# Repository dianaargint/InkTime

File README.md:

# InkTime

InkTime este un smartwatch open-source cu consum redus, realizat in jurul microcontroller-ului **nRF52840**. Proiectul include un **display e-paper**, alimentare din **baterie Li-Po**, **incarcare prin USB-C**, **monitorizare baterie**, **IMU** si **feedback haptic**.

Scopul proiectului a fost realizarea unei placi compacte care sa poata fi integrata intr-o carcasa dedicata si sa poata functiona din baterie, cu un consum cat mai mic.

# Diagrama bloc

```text
+-------------+      +----------------+      +------------------+
| USB-C       |----->| ESD Protection |----->| BQ25180 Charger  |
+-------------+      +----------------+      +--------+---------+
                                                        |
                                                        v
                                                +---------------+
                                                | Li-Po Battery |
                                                +---+-------+---+
                                                    |       |
                                                    |       v
                                                    |   +-----------+
                                                    |   | MAX17048  |
                                                    |   | FuelGauge |
                                                    |   +-----------+
                                                    v
                                              +-------------+
                                              | RT6160 DC/DC|
                                              +------+------+ 
                                                     |
                                                     v
                                              +-------------+
                                              | nRF52840    |
                                              | BLE MCU     |
                                              +------+------+-------------------+
                                                     |      |         |         |
                                                     |      |         |         |
                                                     v      v         v         v
                                              +--------+ +------+ +-------+ +--------+
                                              | E-Paper| | IMU  | |Haptic | | Buttons|
                                              +--------+ +------+ +---+---+ +--------+
                                                                        |
                                                                        v
                                                                   +---------+
                                                                   | Shaker  |
                                                                   +---------+

```

## Bill of Materials (BOM)

| Component | Value / Part Number | Package | Qty | Description | Datasheet |
| --------- | ------------------- | ------- | --- | ----------- | --------- |
| MCU | NRF52840_QF | NORDIC_NRF_4_AQFN50P700X700X85_HS-74N | 1 | Main BLE microcontroller | [Datasheet](https://infocenter.nordicsemi.com/pdf/nRF52840_PS_v1.1.pdf) |
| PMIC charger | BQ25180YBGR | BQ25180YBGR_BGA8C40P2X4_100X155X50 | 1 | Li-Po charger | [Datasheet](https://www.ti.com/lit/ds/symlink/bq25180.pdf) |
| DC/DC | RT6160AWSC | RT6160AWSC_BGA15C40P3X5_140X230X60 | 1 | Buck-boost DC/DC converter | [Datasheet](https://www.richtek.com/assets/product_file/RT6160A/DS6160A-05.pdf) |
| Fuel gauge | MAX17048G+T10 | ESP32_C6_LIBRARY_SON50P200X200X80-9N | 1 | Battery fuel gauge | [Datasheet](https://www.analog.com/media/en/technical-documentation/data-sheets/max17048-max17049.pdf) |
| IMU | BMA421 | BMA423_BMA423 | 1 | Triaxial accelerometer | [Datasheet](https://www.bosch-sensortec.com/products/motion-sensors/accelerometers/bma421/) |
| Haptic driver | DRV2605YZFR | DRV2605YZFR_BGA9C50P3X3_144X144X62 | 1 | Haptic driver for vibration motor | [Datasheet](https://www.ti.com/lit/ds/symlink/drv2605.pdf) |
| USB ESD | USBLC6-2SC6Y | ESP32_C6_LIBRARY_3_SOT95P280X145-6N | 1 | USB ESD protection | [Datasheet](https://www.st.com/resource/en/datasheet/usblc6-2.pdf) |
| Antenna | 2450AT18B100E | 2450AT18B100E_ANTC3216X140N | 1 | 2.4 GHz chip antenna | [Datasheet](https://www.johansontechnology.com/datasheets/antennas/2450AT18B100.pdf) |
| Display connector | 503480-2400 | 503480-2400_5034802400 | 1 | FPC connector for e-paper display | [Datasheet](https://www.molex.com/en-us/products/part-detail/5034802400) |
| USB-C | KH-TYPE-C-16P | KH-TYPE-C-16P_KINGHELM_KH-TYPE-C-16P | 1 | USB-C connector | - |
| Debug connector | TC2030-IDC | TC2030-IDC_TC2030IDC | 1 | SWD programming / debug connector | [Datasheet](https://www.tag-connect.com/product/tc2030-idc) |
| EPD MOSFET | SI1308EDL-T1-GE3 | ESP32_C6_LIBRARY_6_SOT65P210X110-3N | 1 | MOSFET used in e-paper drive stage | [Datasheet](https://www.vishay.com/docs/68986/si1308edl.pdf) |
| EPD MOSFET | DMG2305UX-7 | ESP32_C6_LIBRARY_4_ESP32_WROVER_SPARKFUN-DISCRETESEMI_MOSFET | 1 | MOSFET used in e-paper drive stage | [Datasheet](https://www.diodes.com/assets/Datasheets/DMG2305UX.pdf) |
| Schottky diode | MBR0530 | ESP32_C6_LIBRARY_5_SOD3716X135N | 3 | Schottky diode used in EPD boost stage | [Datasheet](https://www.onsemi.com/pdf/datasheet/mbr0530t1-d.pdf) |
| Power inductor | FTC252012SR47MBCA | MLP2016SR47MT0S1_INDC2016X100N | 1 | Inductor for RT6160 converter | [JLC Part](https://jlcpcb.com/partdetail/6763488-FTC252012SR47MBCA/C5832368) |
| EPD inductor | 68uH | ESP32_C6_LIBRARY_2_IND_4828-WE-TPC_WRE | 1 | Inductor for e-paper boost stage | - |
| RF inductor | 3.9nH | NORDIC_NRF_2_RESC0402_L | 1 | RF matching network | - |
| RF inductor | 15nH | NORDIC_NRF_2_RESC0402_L | 1 | RF filter / matching | - |
| Power inductor | 10uH | NORDIC_NRF_2_RESC0402_L | 1 | Power stage passive | - |
| HF crystal | 32MHz | NORDIC_NRF_BT-XTAL_2016_N | 1 | Main MCU clock | - |
| LF crystal | 32.768kHz | NORDIC_NRF_1_XTAL_3215_N | 1 | RTC / low-power clock | - |
| Buttons | EVP-AKE31A | 2025-10-22_07-23-44_LIBRARY_SW_EVP-AKE31A_PAN | 3 | Tactile user buttons | - |
| Solder jumper | SJ | ESP32_C6_LIBRARY_7_JUMPER_SJ | 1 | Configuration jumper | - |
| Test pads | HECTOR_WATCH_1_TPTP20R | HECTOR_WATCH_1_TP20R | 14 | Test points for debug / power / signals | - |

BOM-ul complet generat automat se gaseste in folderul Manufacturing.

## Pinii folositi de nRF52840

| Pin nRF52840 | Semnal | Componenta / destinatie | Rol |
| ------------ | ------ | ----------------------- | --- |
| P0.00 / XL1 | XL1 | Cristal 32.768kHz | clock low-power / RTC |
| P0.01 / XL2 | XL2 | Cristal 32.768kHz | clock low-power / RTC |
| P0.02 | SCK | Display e-paper | SPI clock pentru display |
| P0.03 | MOSI | Display e-paper | SPI data pentru display |
| P0.05 | EPD_CS | Display e-paper | chip select pentru display |
| P0.06 | SDA | BMA421 / DRV2605 / MAX17048 / BQ25180 / RT6160 | magistrala I2C comuna |
| P0.07 | SCL | BMA421 / DRV2605 / MAX17048 / BQ25180 / RT6160 | magistrala I2C comuna |
| P0.08 | IMU_INT1 | BMA421 | interrupt de la IMU |
| P0.10 | ALERT | MAX17048 | alerta fuel gauge |
| P0.11 | PMIC_INT | BQ25180YBGR | interrupt de la charger |
| P0.12 | HAPTIC_EN | DRV2605YZFR | enable pentru driverul haptic |
| P0.13 | SW_UP | Buton UP | input utilizator |
| P0.14 | SW_ENT | Buton ENTER | input utilizator |
| P0.15 | EPD_DC | Display e-paper | selectare data / command |
| P0.16 | EPD_RST | Display e-paper | reset display |
| P0.17 | EPD_BUSY | Display e-paper | busy status de la display |
| P0.18 / RESET | RESET | Sistem | reset hardware |
| P1.00 | SWO | Debug | trace output |
| P1.02 | SW_DN | Buton DOWN | input utilizator |
| P1.08 | IMU_INT2 | BMA421 | al doilea interrupt de la IMU |
| SWDIO | SWDIO | TC2030-IDC | programare / debug |
| SWDCLK | SWDCLK | TC2030-IDC | programare / debug |
| ANT | RF | Antena 2.4 GHz | transmisie BLE |
| VBUS | VBUS | USB-C | alimentare 5V |

Am ales pinii in asa fel incat sa separ cat mai clar liniile de comunicatie de semnalele de control. Display-ul foloseste SPI pentru transferul de date, iar semnalele EPD_CS, EPD_DC, EPD_RST si EPD_BUSY sunt separate pentru controlul corect al panoului. IMU-ul, fuel gauge-ul, charger-ul, convertorul DC/DC si driverul haptic folosesc aceeasi magistrala I2C, ceea ce reduce numarul de pini ocupati. Butoanele sunt puse pe GPIO-uri dedicate, iar liniile SWDIO, SWDCLK si SWO sunt folosite pentru programare si debugging.

## Descriere hardware
1. Microcontroller

Microcontroller-ul principal al proiectului este nRF52840 (U1). Acesta este componenta centrala a sistemului si se ocupa de:

comunicatia BLE, controlul display-ului e-paper, comunicatia cu senzorii si circuitele de power prin I2C, citirea butoanelor, controlul driverului haptic, interfata de debug SWD

Pentru clock sunt folosite doua cristale:

X1 = 32MHz
X2 = 32.768kHz

Cristalul de 32MHz este folosit pentru functionarea principala a MCU-ului si pentru partea de radio, iar cristalul de 32.768kHz este folosit pentru RTC si modurile low-power.

2. Alimentare si management energetic

Partea de alimentare am impartit-o in trei blocuri principale:

BQ25180YBGR

IC1 = BQ25180YBGR se ocupa de incarcarea bateriei Li-Po din USB-C. Intrarea de 5V vine din VBUS, iar iesirea merge spre baterie. Circuitul are si semnal de interrupt catre MCU pentru monitorizarea starii de incarcare.

MAX17048

U3 = MAX17048G+T10 monitorizeaza tensiunea bateriei si comunica prin I2C cu nRF52840. Are si semnal de alerta catre MCU pentru praguri critice sau schimbari de stare.

RT6160AWSC

IC9 = RT6160AWSC este convertorul buck-boost care genereaza alimentarea stabila 3V3 / VREG pentru sistem. Acesta este necesar deoarece tensiunea bateriei variaza in functie de starea de incarcare, iar sistemul are nevoie de o alimentare stabila.

3. Bateria

Am folosit o baterie de tip LP502030, 3.7V, aproximativ 250mAh. In proiect, bateria nu este conectata prin conector JST, ci direct la doua test pad-uri:

TP_VBAT, TP_BAT_GND

Am ales varianta asta ca sa economisesc spatiu si pentru ca asta era si cerinta proiectului.

4. Display e-paper

Display-ul este conectat prin conectorul 503480-2400 si este controlat prin:

SCK, MOSI, EPD_CS,EPD_DC, EPD_RST, EPD_BUSY

5. IMU

IMU-ul folosit este BMA421 (IC3) si comunica prin I2C. Are doua semnale de interrupt:

IMU_INT1
,IMU_INT2

Aceste semnale sunt conectate la MCU pentru detectarea rapida a evenimentelor de miscare si pentru trezirea sistemului din moduri low-power.

6. Haptic

Pentru feedback haptic este folosit DRV2605YZFR (IC2), care comanda motorul de vibratie. Comunicarea este facuta pe I2C, iar activarea poate fi controlata si printr-un semnal GPIO dedicat.

7. USB-C si protectie ESD

Conectorul J4 = KH-TYPE-C-16P este folosit pentru alimentare si optional pentru interfata USB. Protectia ESD este facuta cu USBLC6-2SC6Y, pentru a proteja liniile sensibile la descarcari electrostatice.

8. RF si antena

Antena este ANT1 = 2450AT18B100E si este conectata la pinul RF al nRF52840 printr-o retea de matching. Antena este pusa la marginea placii, iar sub ea am lasat zona fara plan de masa si fara trasee, conform regulilor de proiectare RF.

## PCB si layout
Board specifications
- dimensiunea placii: 46 mm x 35 mm
- grosimea PCB-ului: 1 mm
- componentele sunt plasate pe TOP
- rutarea este facuta pe Top si Bottom
- exista poligoane de GND pe Top si Bottom
  
Routing rules

- traseele de semnal au fost rutate cu minimum 0.15 mm
- traseele de putere au fost rutate cu 0.3 mm acolo unde spatiul a permis
- in zonele foarte dense, unele segmente scurte au trebuit ingustate local
  
Ground planes

Am folosit planuri de masa pe placa, iar in zonele importante am pus si via stitching, mai ales in jurul zonei RF si al microcontroller-ului.

Antena si keepout

Antena este pusa la marginea PCB-ului, iar sub ea:

- nu exista plan de masa
- nu exista trasee
- nu exista turnare de cupru

Acest lucru a fost facut pentru a nu afecta performanta RF.
Pe parcursul proiectarii au aparut mai multe probleme, mai ales in zonele cu densitate mare de componente:

- zona din jurul nRF52840 a fost dificil de rutat
- integrarea bateriei, display-ului si shaker-ului in acelasi volum a fost dificila

## Integrare mecanica si 3D

In modelul 3D au fost incluse:
- PCB-ul
- carcasa
- bateria
- display-ul
- shaker-ul

Au fost verificate:
- alinierea USB-C
- alinierea butoanelor
- pozitia display-ului fata de carcasa
- spatiul pentru baterie si shaker

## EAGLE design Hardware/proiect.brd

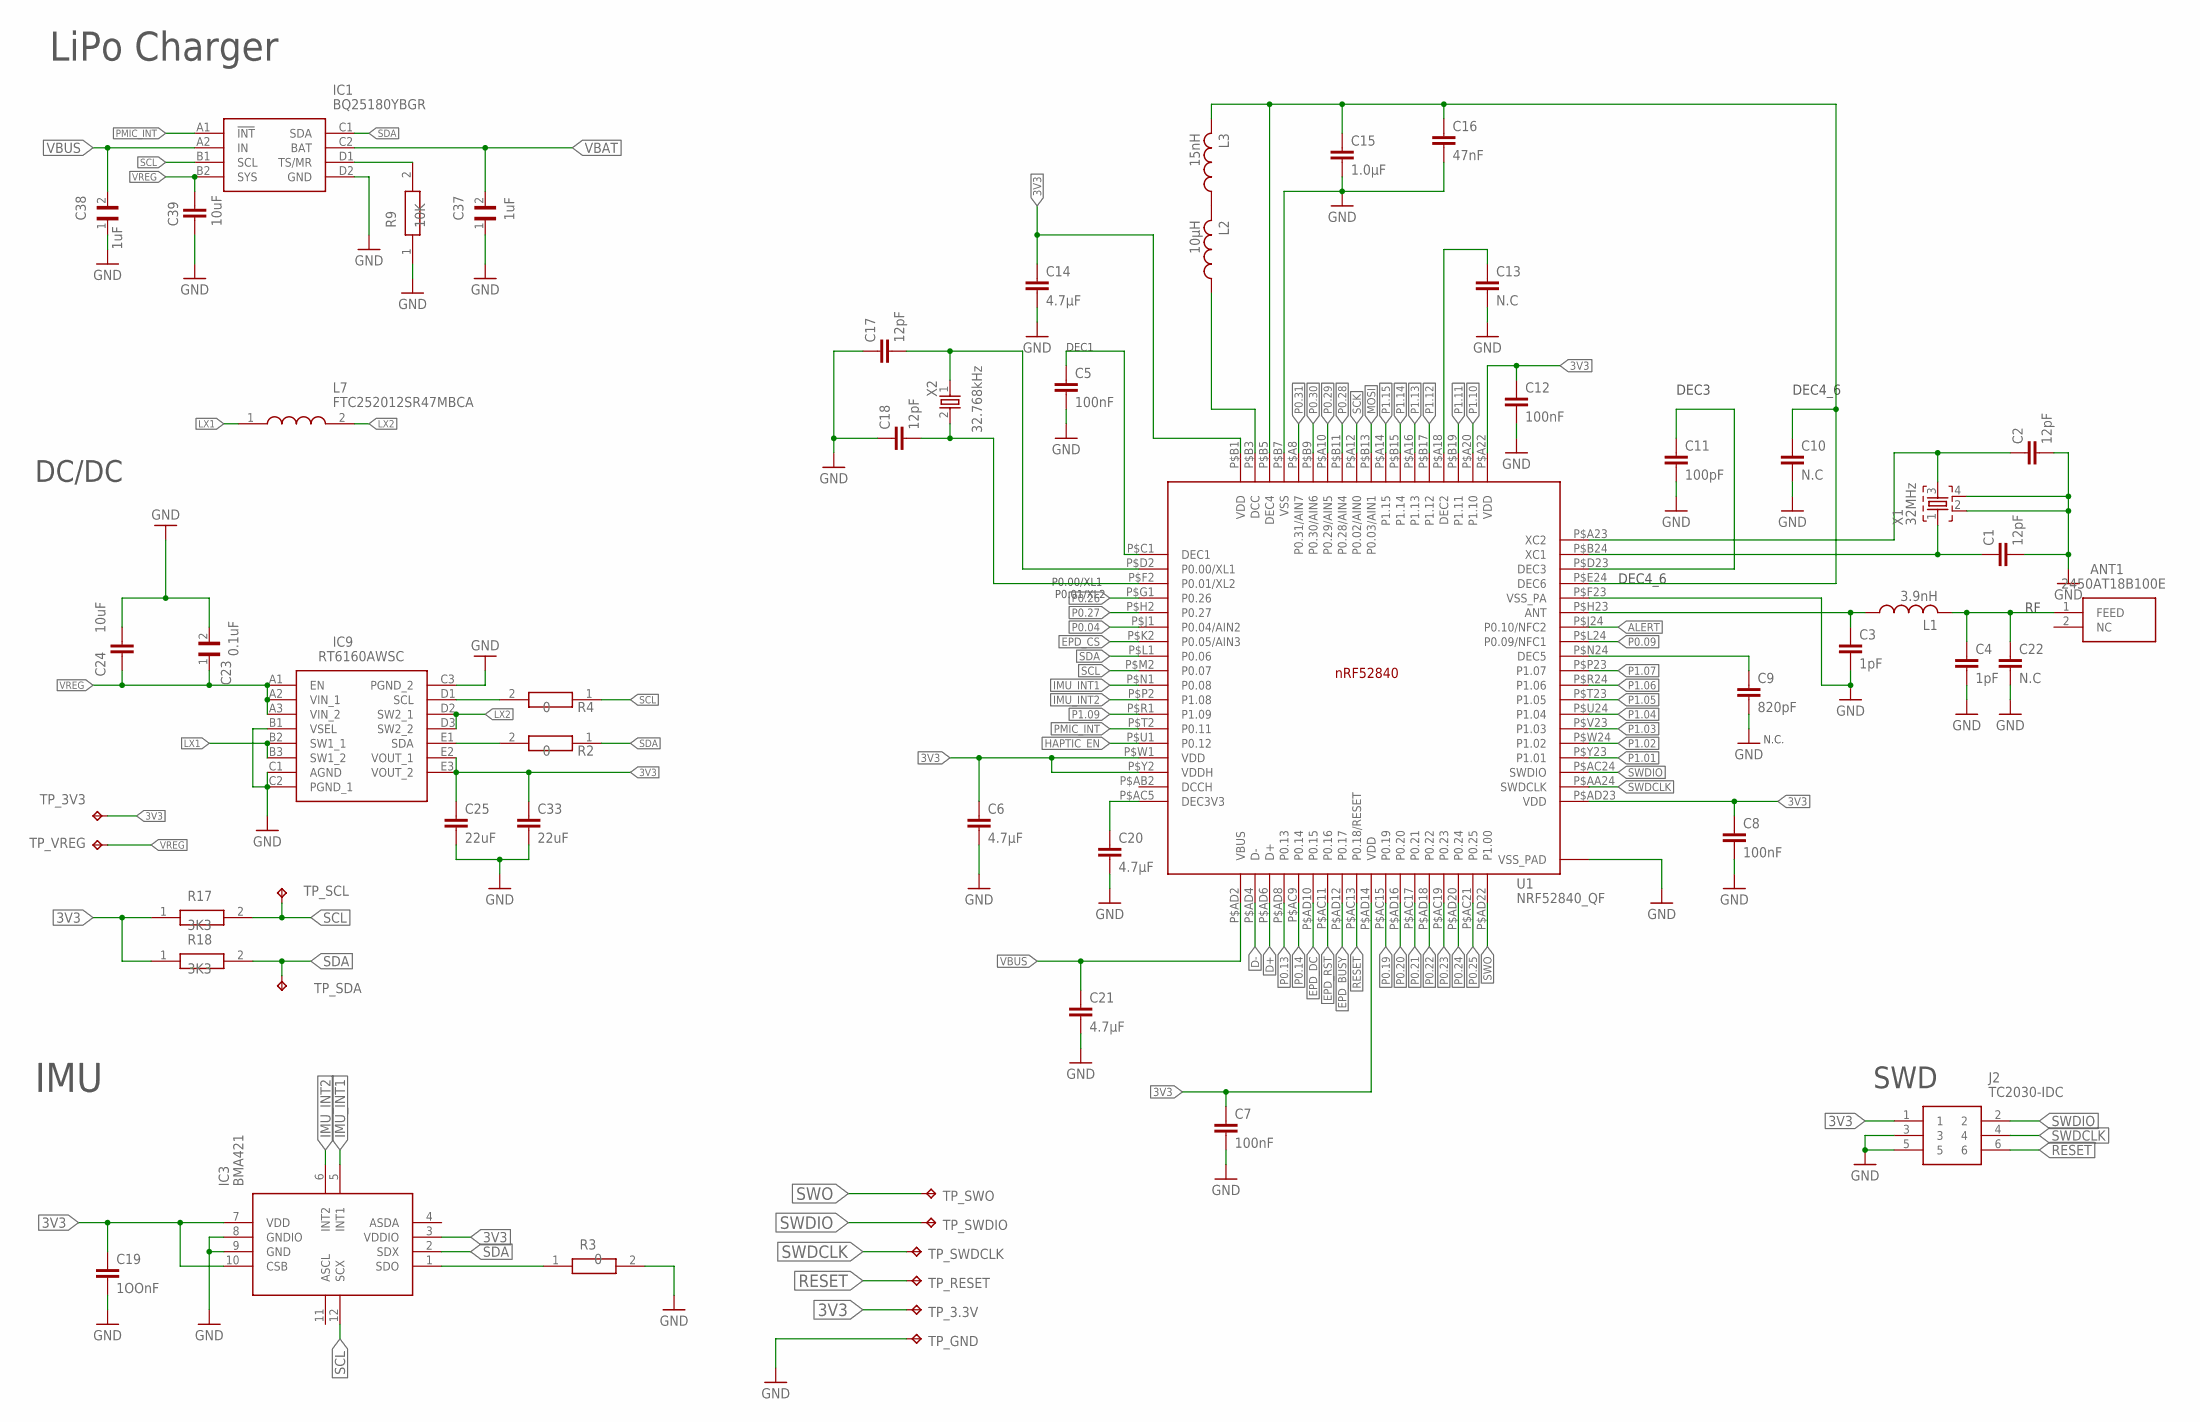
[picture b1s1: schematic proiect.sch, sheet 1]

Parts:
ANT1: 2450AT18B100E; 2450AT18B100E_ANTC3216X140N
C1, C2, C17, C18: 12pF; NORDIC_NRF_3_RESC0201_L
C3, C4: 1pF; NORDIC_NRF_3_RESC0201_L
C5, C7, C8, C12: 100nF; NORDIC_NRF_3_RESC0201_L
C6, C14, C20, C21: 4.7µF; PERFECT_0402_0402
C9: 820pF; NORDIC_NRF_3_RESC0201_L
C10, C13, C22: N.C; NORDIC_NRF_3_RESC0201_L
C11: 100pF; NORDIC_NRF_3_RESC0201_L
C15: 1.0µF; PERFECT_0402_0402
C16: 47nF; NORDIC_NRF_3_RESC0201_L
C19: 1OOnF; NORDIC_NRF_3_RESC0201_L
C23: 0.1uF; GRM011R60J152KE01L_2_CAPC0201X13N
C24, C39: 10uF; PERFECT_0402_0402
C25, C33: 22uF; PERFECT_0402_0402
C37, C38: 1uF; GRM011R60J152KE01L_2_CAPC0201X13N
IC1: BQ25180YBGR; BQ25180YBGR_BGA8C40P2X4_100X155X50
IC3: BMA421; BMA423_BMA423
IC9: RT6160AWSC; RT6160AWSC_BGA15C40P3X5_140X230X60
J2: TC2030-IDC; TC2030-IDC_TC2030IDC
L1: 3.9nH; NORDIC_NRF_2_RESC0402_L
L2: 10µH; NORDIC_NRF_2_RESC0402_L
L3: 15nH; NORDIC_NRF_2_RESC0402_L
L7: FTC252012SR47MBCA; MLP2016SR47MT0S1_INDC2016X100N
R2, R3, R4: 0; CPF0201D7K68C1_0201
R9: 10K; CPF0201D7K68C1_0201
R17, R18: 3K3; CPF0201D7K68C1_0201
TP_3.3V, TP_3V3: HECTOR_WATCH_1_TPTP20R; HECTOR_WATCH_1_TP20R
TP_GND: HECTOR_WATCH_1_TPTP20R; HECTOR_WATCH_1_TP20R
TP_RESET: HECTOR_WATCH_1_TPTP20R; HECTOR_WATCH_1_TP20R
TP_SCL: HECTOR_WATCH_1_TPTP20R; HECTOR_WATCH_1_TP20R
TP_SDA: HECTOR_WATCH_1_TPTP20R; HECTOR_WATCH_1_TP20R
TP_SWDCLK: HECTOR_WATCH_1_TPTP20R; HECTOR_WATCH_1_TP20R
TP_SWDIO: HECTOR_WATCH_1_TPTP20R; HECTOR_WATCH_1_TP20R
TP_SWO: HECTOR_WATCH_1_TPTP20R; HECTOR_WATCH_1_TP20R
TP_VREG: HECTOR_WATCH_1_TPTP20R; HECTOR_WATCH_1_TP20R
U1: NRF52840_QF; NORDIC_NRF_4_AQFN50P700X700X85_HS-74N
X1: 32MHz; NORDIC_NRF_BT-XTAL_2016_N
X2: 32.768kHz; NORDIC_NRF_1_XTAL_3215_N

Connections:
3V3: C6.1, C7.1, C8.1, C12.1, C14.1, C19.1, C25.1, C33.1, IC3.3 (VDDIO), IC3.7 (VDD), IC3.10 (CSB), IC9.E2 (VOUT_1), IC9.E3 (VOUT_2), J2.1, R17.1, R18.1, TP_3.3V.TP, TP_3V3.TP, U1.P$A22 (VDD), U1.P$AD14 (VDD), U1.P$AD23 (VDD), U1.P$B1 (VDD), U1.P$W1 (VDD), U1.P$Y2 (VDDH); also elsewhere on the board
ALERT: U1.P$J24 (P0.10/NFC2); also elsewhere on the board
D+: U1.P$AD6 (D+); also elsewhere on the board
D-: U1.P$AD4 (D-); also elsewhere on the board
EPD_BUSY: U1.P$AD12 (P0.17); also elsewhere on the board
EPD_CS: U1.P$K2 (P0.05/AIN3); also elsewhere on the board
EPD_DC: U1.P$AD10 (P0.15); also elsewhere on the board
EPD_RST: U1.P$AC11 (P0.16); also elsewhere on the board
GND: C1.2, C2.2, C3.2, C4.2, C5.2, C6.2, C7.2, C8.2, C9.2, C10.2, C11.2, C12.2, C13.2, C14.2, C15.2, C16.2, C17.1, C18.1, C19.2, C20.2, C21.2, C22.2, C23.2, C24.1, C25.2, C33.2, C37.1, C38.1, C39.2, IC1.D2 (GND), IC3.8 (GNDIO), IC3.9 (GND), IC9.B1 (VSEL), IC9.C1 (AGND), IC9.C2 (PGND_1), IC9.C3 (PGND_2), J2.3, J2.5, R3.2, R9.1, TP_GND.TP, U1.P$74 (VSS_PAD), U1.P$75 (VSS_PAD), U1.P$76 (VSS_PAD), U1.P$77 (VSS_PAD), U1.P$78 (VSS_PAD), U1.P$79 (VSS_PAD), U1.P$80 (VSS_PAD), U1.P$81 (VSS_PAD), U1.P$82 (VSS_PAD), U1.P$83 (VSS_PAD), U1.P$84 (VSS_PAD), U1.P$85 (VSS_PAD), U1.P$86 (VSS_PAD), U1.P$87 (VSS_PAD), U1.P$88 (VSS_PAD), U1.P$89 (VSS_PAD), U1.P$90 (VSS_PAD), U1.P$B7 (VSS), U1.P$F23 (VSS_PA), X1.2, X1.4; also elsewhere on the board
HAPTIC_EN: U1.P$U1 (P0.12); also elsewhere on the board
IMU_INT1: IC3.5 (INT1), U1.P$N1 (P0.08)
IMU_INT2: IC3.6 (INT2), U1.P$P2 (P1.08)
LX1: IC9.B2 (SW1_1), IC9.B3 (SW1_2), L7.1
LX2: IC9.D2 (SW2_1), IC9.D3 (SW2_2), L7.2
MOSI: U1.P$B13 (P0.03/AIN1); also elsewhere on the board
unnamed: C3.1, L1.1, U1.P$H23 (ANT)
unnamed: IC9.D1 (SCL), R4.2
unnamed: IC1.D1 (TS/MR), R9.2
unnamed: C9.1, U1.P$N24 (DEC5)
unnamed: IC9.E1 (SDA), R2.2
unnamed: ANT1.1 (FEED), C4.1, C22.1, L1.2
unnamed: C11.1, U1.P$D23 (DEC3)
unnamed: IC3.1 (SDO), R3.1
unnamed: L2.2, L3.1
unnamed: C20.1, U1.P$AC5 (DEC3V3)
unnamed: C5.1, U1.P$C1 (DEC1)
unnamed: C17.2, U1.P$D2 (P0.00/XL1), X2.1
unnamed: C18.2, U1.P$F2 (P0.01/XL2), X2.2
unnamed: C1.1, U1.P$B24 (XC1), X1.1
unnamed: C2.1, U1.P$A23 (XC2), X1.3
unnamed: C10.1, C15.1, C16.1, L3.2, U1.P$B5 (DEC4), U1.P$E24 (DEC6)
unnamed: C13.1, U1.P$A18 (DEC2)
unnamed: L2.1, U1.P$B3 (DCC)
P0.04: U1.P$J1 (P0.04/AIN2)
P0.09: U1.P$L24 (P0.09/NFC1)
P0.13: U1.P$AD8 (P0.13); also elsewhere on the board
P0.14: U1.P$AC9 (P0.14); also elsewhere on the board
P0.19: U1.P$AC15 (P0.19)
P0.20: U1.P$AD16 (P0.20)
P0.21: U1.P$AC17 (P0.21)
P0.22: U1.P$AD18 (P0.22)
P0.23: U1.P$AC19 (P0.23)
P0.24: U1.P$AD20 (P0.24)
P0.25: U1.P$AC21 (P0.25)
P0.26: U1.P$G1 (P0.26)
P0.27: U1.P$H2 (P0.27)
P0.28: U1.P$B11 (P0.28/AIN4)
P0.29: U1.P$A10 (P0.29/AIN5)
P0.30: U1.P$B9 (P0.30/AIN6)
P0.31: U1.P$A8 (P0.31/AIN7)
P1.01: U1.P$Y23 (P1.01); also elsewhere on the board
P1.02: U1.P$W24 (P1.02); also elsewhere on the board
P1.03: U1.P$V23 (P1.03)
P1.04: U1.P$U24 (P1.04)
P1.05: U1.P$T23 (P1.05)
P1.06: U1.P$R24 (P1.06)
P1.07: U1.P$P23 (P1.07)
P1.09: U1.P$R1 (P1.09)
P1.10: U1.P$A20 (P1.10)
P1.11: U1.P$B19 (P1.11)
P1.12: U1.P$B17 (P1.12)
P1.13: U1.P$A16 (P1.13)
P1.14: U1.P$B15 (P1.14)
P1.15: U1.P$A14 (P1.15)
PMIC_INT: IC1.A1 (!INT), U1.P$T2 (P0.11)
RESET: J2.6, TP_RESET.TP, U1.P$AC13 (P0.18/RESET)
SCK: U1.P$A12 (P0.02/AIN0); also elsewhere on the board
SCL: IC1.B1 (SCL), IC3.12 (SCX), R4.1, R17.2, TP_SCL.TP, U1.P$M2 (P0.07); also elsewhere on the board
SDA: IC1.C1 (SDA), IC3.2 (SDX), R2.1, R18.2, TP_SDA.TP, U1.P$L1 (P0.06); also elsewhere on the board
SWDCLK: J2.4, TP_SWDCLK.TP, U1.P$AA24 (SWDCLK)
SWDIO: J2.2, TP_SWDIO.TP, U1.P$AC24 (SWDIO)
SWO: TP_SWO.TP, U1.P$AD22 (P1.00)
VBAT: C37.2, IC1.C2 (BAT); also elsewhere on the board
VBUS: C21.1, C38.2, IC1.A2 (IN), U1.P$AD2 (VBUS); also elsewhere on the board
VREG: C23.1, C24.2, C39.1, IC1.B2 (SYS), IC9.A1 (EN), IC9.A2 (VIN_1), IC9.A3 (VIN_2), TP_VREG.TP

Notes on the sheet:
SWD
LiPo Charger
IMU
DC/DC
N.C.
DEC1
P0.00/XL1 P0.01/XL2
DEC3
DEC4_6

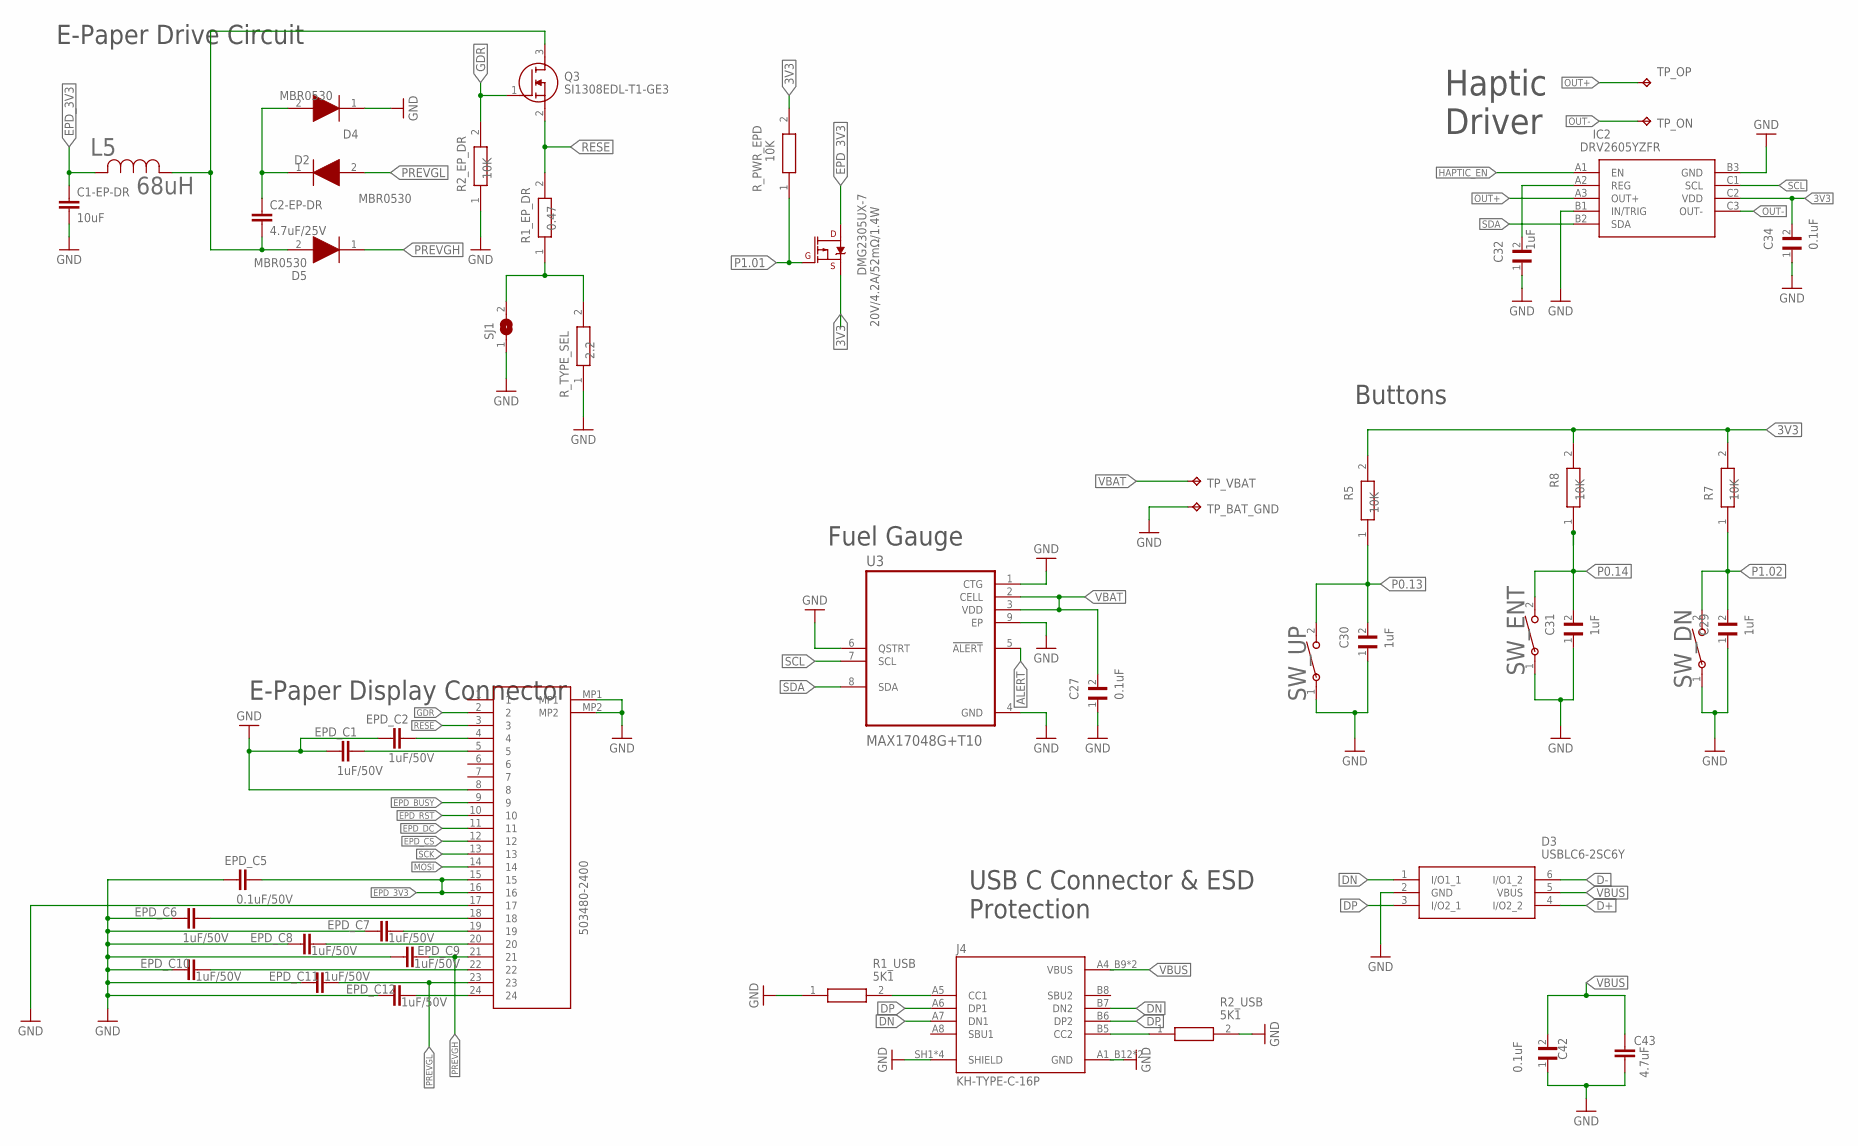
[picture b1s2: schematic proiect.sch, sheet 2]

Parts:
503480-2400: 503480-2400_503480-2400; 503480-2400_5034802400
C1-EP-DR: 10uF; PERFECT_0402_0402
C2-EP-DR: 4.7uF/25V; PERFECT_0402_0402
C27, C34, C42: 0.1uF; GRM011R60J152KE01L_2_CAPC0201X13N
C29, C30, C31, C32: 1uF; GRM011R60J152KE01L_2_CAPC0201X13N
C43: 4.7uF; PERFECT_0402_0402
D2, D4, D5: MBR0530; ESP32_C6_LIBRARY_5_SOD3716X135N
D3: USBLC6-2SC6Y; ESP32_C6_LIBRARY_3_SOT95P280X145-6N
DMG2305UX-7: 20V/4.2A/52mΩ/1.4W; ESP32_C6_LIBRARY_4_ESP32_C6_LIBRARY_4_ESP32_C6_LIBRARY_4_ES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
EPD_C1, EPD_C2, EPD_C6, EPD_C7, EPD_C8, EPD_C9, EPD_C10, EPD_C11, EPD_C12: 1uF/50V; PERFECT_0402_0402
EPD_C5: 0.1uF/50V; NORDIC_NRF_3_RESC0201_L
IC2: DRV2605YZFR; DRV2605YZFR_BGA9C50P3X3_144X144X62
J4: KH-TYPE-C-16P; KH-TYPE-C-16P_KINGHELM_KH-TYPE-C-16P
L5: 68uH; ESP32_C6_LIBRARY_2_IND_4828-WE-TPC_WRE
Q3: SI1308EDL-T1-GE3; ESP32_C6_LIBRARY_6_SOT65P210X110-3N
R1_EP_DR: 0.47; CPF0201D7K68C1_0201
R1_USB, R2_USB: 5K1; CPF0201D7K68C1_0201
R2_EP_DR, R5, R7, R8: 10K; CPF0201D7K68C1_0201
R_PWR_EPD: 10K; CPF0201D7K68C1_0201
R_TYPE_SEL: 2.2; CPF0201D7K68C1_0201
SJ1: ESP32_C6_LIBRARY_7_JUMPER_SJ
SW_DN: 2025-10-22_07-23-44_LIBRARY_EVP-AKE31ASW_EVP-AKE3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; 2025-10-22_07-23-44_LIBRARY_SW_EVP-AKE31A_PAN
SW_ENT: 2025-10-22_07-23-44_LIBRARY_EVP-AKE31ASW_EVP-AKE3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; 2025-10-22_07-23-44_LIBRARY_SW_EVP-AKE31A_PAN
SW_UP: 2025-10-22_07-23-44_LIBRARY_EVP-AKE31ASW_EVP-AKE3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; 2025-10-22_07-23-44_LIBRARY_SW_EVP-AKE31A_PAN
TP_BAT_GND: HECTOR_WATCH_1_TPTP20R; HECTOR_WATCH_1_TP20R
TP_ON: HECTOR_WATCH_1_TPTP20R; HECTOR_WATCH_1_TP20R
TP_OP: HECTOR_WATCH_1_TPTP20R; HECTOR_WATCH_1_TP20R
TP_VBAT: HECTOR_WATCH_1_TPTP20R; HECTOR_WATCH_1_TP20R
U3: MAX17048G+T10; ESP32_C6_LIBRARY_SON50P200X200X80-9N

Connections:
3V3: C34.2, DMG2305UX-7.2 (S), IC2.C2 (VDD), R5.2, R7.2, R8.2, R_PWR_EPD.2; also elsewhere on the board
ALERT: U3.5 (!ALERT); also elsewhere on the board
D+: D3.4 (I/O2_2); also elsewhere on the board
D-: D3.6 (I/O1_2); also elsewhere on the board
DN: D3.1 (I/O1_1), J4.A7 (DN1), J4.B7 (DN2)
DP: D3.3 (I/O2_1), J4.A6 (DP1), J4.B6 (DP2)
EPD_3V3: 503480-2400.15, 503480-2400.16, C1-EP-DR.1, DMG2305UX-7.3 (D), EPD_C5.2, L5.2
EPD_BUSY: 503480-2400.9; also elsewhere on the board
EPD_CS: 503480-2400.12; also elsewhere on the board
EPD_DC: 503480-2400.11; also elsewhere on the board
EPD_RST: 503480-2400.10; also elsewhere on the board
GDR: 503480-2400.2, Q3.1 (G), R2_EP_DR.2
GND: 503480-2400.8, 503480-2400.17, 503480-2400.MP1, 503480-2400.MP2, C1-EP-DR.2, C27.1, C29.1, C30.1, C31.1, C32.1, C34.1, C42.1, C43.2, D3.2 (GND), D4.1 (K), EPD_C1.1, EPD_C2.1, EPD_C5.1, EPD_C6.1, EPD_C7.1, EPD_C8.1, EPD_C9.1, EPD_C10.1, EPD_C11.1, EPD_C12.1, IC2.B1 (IN/TRIG), IC2.B3 (GND), J4.A1_B12 (GND), J4.A12_B1 (GND), J4.SH1 (SHIELD), J4.SH2 (SHIELD), J4.SH3 (SHIELD), J4.SH4 (SHIELD), R1_USB.1, R2_EP_DR.1, R2_USB.2, R_TYPE_SEL.1, SJ1.1, SW_DN.1, SW_ENT.1, SW_UP.1, TP_BAT_GND.TP, U3.1 (CTG), U3.4 (GND), U3.6 (QSTRT), U3.9 (EP); also elsewhere on the board
HAPTIC_EN: IC2.A1 (EN); also elsewhere on the board
MOSI: 503480-2400.14; also elsewhere on the board
unnamed: C2-EP-DR.2, D5.2 (A), L5.1, Q3.3 (D)
unnamed: C2-EP-DR.1, D2.1 (K), D4.2 (A)
unnamed: R1_EP_DR.1, R_TYPE_SEL.2, SJ1.2
unnamed: 503480-2400.5, EPD_C1.2
unnamed: 503480-2400.4, EPD_C2.2
unnamed: 503480-2400.18, EPD_C6.2
unnamed: C32.2, IC2.A2 (REG)
unnamed: 503480-2400.19, EPD_C7.2
unnamed: 503480-2400.20, EPD_C8.2
unnamed: 503480-2400.22, EPD_C10.2
unnamed: 503480-2400.24, EPD_C12.2
unnamed: J4.A5 (CC1), R1_USB.2
unnamed: J4.B5 (CC2), R2_USB.1
OUT+: IC2.A3 (OUT+), TP_OP.TP
OUT-: IC2.C3 (OUT-), TP_ON.TP
P0.13: C30.2, R5.1, SW_UP.2; also elsewhere on the board
P0.14: C31.2, R8.1, SW_ENT.2; also elsewhere on the board
P1.01: DMG2305UX-7.1 (G), R_PWR_EPD.1; also elsewhere on the board
P1.02: C29.2, R7.1, SW_DN.2; also elsewhere on the board
PREVGH: 503480-2400.21, D5.1 (K), EPD_C9.2
PREVGL: 503480-2400.23, D2.2 (A), EPD_C11.2
RESE: 503480-2400.3, Q3.2 (S), R1_EP_DR.2
SCK: 503480-2400.13; also elsewhere on the board
SCL: IC2.C1 (SCL), U3.7 (SCL); also elsewhere on the board
SDA: IC2.B2 (SDA), U3.8 (SDA); also elsewhere on the board
VBAT: C27.2, TP_VBAT.TP, U3.2 (CELL), U3.3 (VDD); also elsewhere on the board
VBUS: C42.2, C43.1, D3.5 (VBUS), J4.A4_B9 (VBUS), J4.A9_B4 (VBUS); also elsewhere on the board

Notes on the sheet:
Haptic Driver
E-Paper Display Connector
E-Paper Drive Circuit
Buttons
Fuel Gauge
USB C Connector & ESD Protection

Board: 2 copper layers, 105 parts (0 on the bottom side), 70 nets, no tracks yet.

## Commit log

2026-04-10 Create LICENSE
2026-04-21 Create Manufacturing
2026-04-22 Rename Captură de ecran 2026-04-22 234811.png to explodedview
2026-04-22 Rename explodedview to explodedview.png
2026-04-22 Rename Captură de ecran 2026-04-23 000929.png to watchassembly.png
2026-04-22 Enhance README with hardware details and BOM
    Updated the README.md file with detailed hardware descriptions, BOM, and pin usage for the nRF52840 microcontroller.

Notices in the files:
parts and their libraries:
COPYRIGHT: Copyright (C) 2024 Ultra Librarian. All rights reserved.
COPYRIGHT: Copyright (C) 2025 Ultra Librarian. All rights reserved.
